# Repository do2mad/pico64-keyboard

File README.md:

# Pico64 Keyboard

> 🇩🇪 **Deutsche Anleitung: [README.de.md](README.de.md)**

A tiny adapter that turns a **Raspberry Pi Pico 2 W** into a wireless keyboard and joystick
interface for the **Commodore 64** – use your phone with the
[Blue-64 Keyboard app](https://github.com/do2mad/blue64-keyboard-ios) (iPhone and Android),
a **Bluetooth keyboard** or a **Bluetooth gamepad** (e.g. 8BitDo).

**Get the app:** iPhone – [TestFlight beta](https://testflight.apple.com/join/jEn4tsP7) · Android – [APK in the latest release](https://github.com/do2mad/blue64-keyboard-ios/releases/latest)

The Pico plugs in between the C64 mainboard and the keyboard cable and emulates the keyboard
matrix in software. Apart from the Pico you only need **17 resistors and one diode** – no level
shifters and no crosspoint switch, because GPIO 0–25 of the RP2350 are 5 V tolerant.
The original keyboard and both joysticks keep working.

## Features

- Emulates the complete 8×8 keyboard matrix plus RESTORE – any number of keys at the same time
- Reacts within about 70 ns to every column the C64 selects (core 1 runs a lookup table from RAM),
  so programs that scan several columns at once work too
- Same Bluetooth LE service as the BT-64 / Blue-64 firmware with the BLE keyboard service –
  the Blue-64 Keyboard app works unchanged (the Pico shows up as **Pico64**)
- Type text and short BASIC listings from the app (snippets)
- **Bluetooth keyboards** (Classic and BLE) – German QWERTZ layout typed as printed, or
  positional mapping for games (F10 switches)
- **Bluetooth gamepads** (8BitDo, Xbox, PlayStation, Switch and many more, via
  [Bluepad32](https://github.com/ricardoquesada/bluepad32)) as **joystick in port 1 or 2**
- App, keyboard and gamepads can be used at the same time; **two app devices** (e.g. iPhone and iPad) at once
- **CBM-II keyboard** by cable or Bluetooth with the [CBM2 Keyboard](https://github.com/do2mad/cbm2-keyboard) adapter (from 0.13.1, socket J3 on the V2 PCB)
- USB keyboard without a C64: the real C64 keyboard on a Mac, PC or MiSTer
- USB console: every line you type in a terminal is typed on the C64, plus a key log for debugging
- Powered by the C64, no extra power supply

## Status

**v0.13.1 – working.** Tested on a breadbin C64 with an iPhone and an Android phone, Bluetooth
keyboards, gamepads and the CBM2 Keyboard. **PCB V2** with the Pico on top (soldered or plugged in)
and the socket for the CBM2 Keyboard – KiCad project, Gerber files, parts list and photos in
[hardware/](hardware/). Bluetooth keyboard and gamepad support still needs testing with more devices.

> **Hardware change in v0.10:** all 17 resistors are now 100 Ω (PA0–PA7 were 1 kΩ). Joystick
> port 2 needs this – everything else also works with the old values. See [docs/HARDWARE.md](docs/HARDWARE.md).

## Getting started

1. **Build the adapter** – PCB (KiCad project, Gerber files, parts list): [hardware/](hardware/); wiring and safety
   notes, also for perfboard: [docs/HARDWARE.md](docs/HARDWARE.md).
   Check the CN1 pinout of your C64 with a multimeter before soldering.
2. **Flash the firmware** – easiest on the [flash page](https://1mhz.de/Pico64/) straight from Chrome
   or Edge. Or: hold BOOTSEL, plug the Pico into your computer, drag
   `pico64-keyboard-vX.Y.Z.uf2` from the [latest release](https://github.com/do2mad/pico64-keyboard/releases/latest)
   onto the `RP2350` drive. Do this with the Pico **out of the C64** or with the C64 switched off.
3. **Plug it in** between CN1 and the keyboard cable, switch the C64 on – the Pico LED blinks
   (nothing connected yet).
4. **Connect with the app** – [Blue-64 Keyboard](https://github.com/do2mad/blue64-keyboard-ios)
   finds the Pico by itself, the LED stays on while connected.
5. **Or pair a Bluetooth keyboard / gamepad** – see below.

Building the firmware yourself: [docs/BUILDING.md](docs/BUILDING.md).
Bluetooth and cable protocol: [docs/PROTOCOL.md](docs/PROTOCOL.md).

## Bluetooth keyboard and gamepad

The Pico looks for keyboards and gamepads all the time. To pair a new one, put it into pairing
mode – it connects by itself within a few seconds (no PIN, no app needed). Paired devices
reconnect automatically when switched on. Up to 4 Bluetooth connections at the same time
(apps, keyboards and gamepads together).

- **Keyboard:** usually hold the Bluetooth / pairing key (or Fn + a channel key) for 3 s, see
  the keyboard's manual. If the keyboard asks for a code, type `0000` and Enter.
- **8BitDo gamepads:** switch on in **Android / D-input mode** (many models: hold **B + Start**)
  or **Switch mode** (**Y + Start**), then hold the pair button for 3 s. Modes differ per model –
  see the 8BitDo manual and the [Bluepad32 list of supported controllers](https://bluepad32.readthedocs.io/).
- **Other gamepads** (Xbox, PlayStation, Switch Pro …): normal pairing mode.

### Keyboard mapping

Two modes, **F10** switches (the USB console shows the current mode):

| Mode | What it does |
|---|---|
| **Symbolic** (default) | Types what is printed on a **German** keyboard: Shift+0 gives `=`, Shift+2 `"`, AltGr+Q `@`, Z and Y in the right place. Characters the C64 doesn't have (ä ö ü ß € …) are ignored. |
| **Positional** | Every key acts like the C64 key at the same place, SHIFT stays SHIFT – best for games and for the graphic characters. |

| PC key | C64 key |
|---|---|
| Esc | RUN/STOP |
| Tab | CTRL |
| Ctrl | CTRL |
| Alt, Windows/Cmd | C= |
| Backspace, Del | INST/DEL |
| Home | CLR/HOME |
| Insert | £ |
| F1 – F8 | F1 – F8 |
| F9, Page Up, Pause | RESTORE |
| Cursor keys | CRSR (up/left with SHIFT automatically) |
| F10 | switch mapping |

### Gamepad

| Gamepad | C64 |
|---|---|
| D-pad or left stick | joystick directions |
| A, B | fire |
| X | SPACE |
| Y | RETURN |
| Select / − | RUN/STOP |
| Start / + | F1 |
| L1 + R1 together | swap joystick port (1 ↔ 2) |

The first gamepad plays on **port 2** (most games), a second one on port 1.

## USB keyboard (without a C64)

Take the board out of the C64, plug the C64 keyboard cable into it and connect the Pico via USB
to a Mac, PC, Raspberry Pi or MiSTer: the **real C64 keyboard becomes a USB keyboard**. The app
and Bluetooth keyboards work at the same time and are sent via USB too.

The Pico decides when it starts: without USB power it can only be powered by the C64 → C64
mode. With USB power it listens for 0.6 s whether a C64 scans the keyboard → C64 mode,
otherwise USB keyboard. If a C64 starts scanning later, the Pico restarts in C64 mode by itself.
A C64 that is switched off but still connected pulls the lines low – the Pico then stays in C64
mode (the USB keyboard only works with the board outside the C64).

Choose the output with **RESTORE + F key** (stored):

| Keys | Output |
|---|---|
| RESTORE + F1 | MiSTer, C64 core (keys as the core expects them; RESTORE alone = F11) |
| RESTORE + F3 | PC, German layout |
| RESTORE + F5 | PC, US layout |
| RESTORE + F7 | Mac, German layout |
| RESTORE + F8 (SHIFT + F7) | Mac, US layout |

PC / Mac: types what is printed on the key (SHIFT + 2 = `"`, SHIFT + `:` = `[`). DEL = Backspace,
INST = Insert, CRSR = cursor keys, F1–F8, HOME / CLR = Home / End, RUN/STOP = Esc, ← = Tab,
CTRL = Ctrl, C= = Win / Cmd, £ = `\`. Like the original, the keyboard has no diodes, so some
three-key combinations show a phantom key.

In the USB console `!u` shows the mode, `!u0` … `!u4` choose the output.

## USB console

Connect the Pico via USB while it sits in the C64 (the diode protects both sides) and open a
terminal with 115200 baud, e.g. `screen /dev/tty.usbmodem* 115200` on a Mac.

- Every line you type is typed on the C64, followed by RETURN (letters unshifted, tokens like
  `~clr~`, `~home~`, `~f1~` work).
- A line with just `d` switches the key log on or off: every key state received via Bluetooth
  and every state applied to the matrix, with timestamps, plus the connection interval.
- `!s` status (app, keyboards, gamepads, joystick ports), `!p` switch keyboard mapping,
  `!b` search for new Bluetooth devices on/off, `!x` forget all paired keyboards / gamepads,
  `!u` USB keyboard mode (see above).

## Safety

- The Pico **never drives a C64 line high** – PB0–PB7, RESTORE and (for joystick 2) PA0–PA4
  are only pulled to GND or released (open drain), like a key switch or a joystick does.
- Use GP0–GP22 only. GP26–GP28 are **not** 5 V tolerant, GP23–25 and GP29 belong to the radio.
- 5 V tolerance only applies while the Pico is powered – which it always is, because it is
  powered by the C64.
- Use at your own risk. Check your wiring twice.

## Related projects

- [Blue-64 Keyboard](https://github.com/do2mad/blue64-keyboard-ios) – the app (iPhone and Android)
- [CBM2 Keyboard](https://github.com/do2mad/cbm2-keyboard) – a CBM-II keyboard (500/600/700) on the C64,
  connected to the Pico64 by cable or Bluetooth
- [Pico USB Keyboard](https://github.com/do2mad/pico-usb-keyboard) – the same app as a USB keyboard:
  a plain Pico 2 W without wiring, for the MiSTer C64 core, PC, Mac or Raspberry Pi
- [BT-64 with BLE keyboard service](https://github.com/do2mad/BT-64/tree/ble-keyboard) – the
  firmware extension for the BT-64 / Blue-64 adapter

## Discussion

Questions, photos, experiences: the thread in the (German) retro forum
[1mhz.de – Pico64-Keyboard, SPL BT-64 oder Blue-64 Tastaturadapter](https://1mhz.de/forum/thread/8761-pico64-keyboard-spl-bt-64-oder-blue-64-tastaturadapter/).
Bug reports and feature requests are also welcome as a GitHub issue.

## Credits & license

- Firmware © 2026 Martin Oswald – [1mhz.de](https://1mhz.de), [MIT License](LICENSE)
- Hardware (schematic, PCB) © 2026 Martin Oswald,
  [CC BY-SA 4.0](LICENSE-HARDWARE.md) – open hardware
- Uses the Raspberry Pi Pico SDK, BTstack, the CYW43 driver and
  [Bluepad32](https://github.com/ricardoquesada/bluepad32) by Ricardo Quesada – see [NOTICE](NOTICE)
- The Bluetooth service follows the protocol of the BLE keyboard extension for
  [BT-64 / Blue-64](https://github.com/sideprojectslab/BT-64) by SideProjectsLab
- C64 keyboard connector pinout after Ruud Baltissen

Changes: [CHANGELOG.md](CHANGELOG.md)

Commodore and Commodore 64 are trademarks of their respective owners. This project is not
affiliated with or endorsed by them, by Raspberry Pi Ltd. or by SideProjectsLab.

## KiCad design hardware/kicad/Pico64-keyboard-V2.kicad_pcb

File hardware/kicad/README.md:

# Pico64 Keyboard – KiCad project (PCB V2)

Open `Pico64-keyboard-V2.kicad_pro` with **KiCad 10**. Everything the project needs is in this
folder: the symbol library `Pico64-keyboard-V2.kicad_sym`, the footprints in
`Pico64-keyboard-V2.pretty/` and the 3D models in `3d/` – the library tables use `${KIPRJMOD}`,
so no global libraries are required.

Licence: CC BY-SA 4.0 (see `../../LICENSE-HARDWARE.md`). The 3D models and several footprints
are based on the KiCad libraries (CC BY-SA 4.0 with the KiCad library exception).

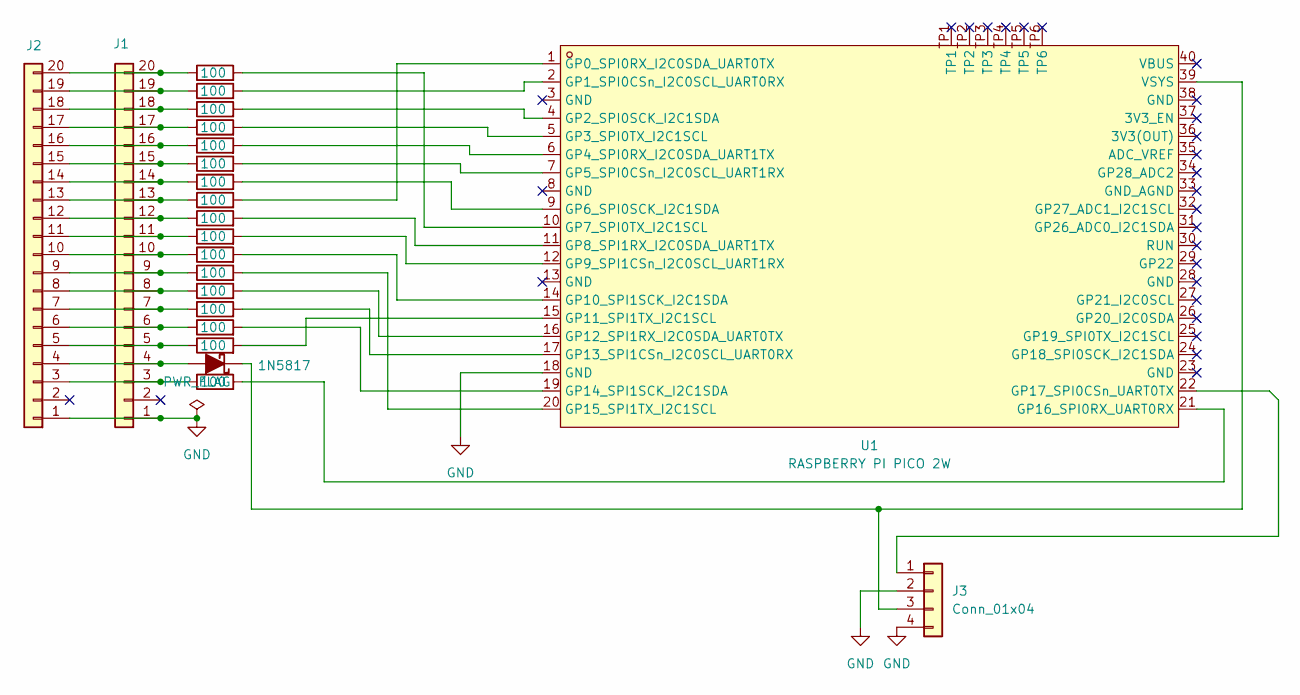
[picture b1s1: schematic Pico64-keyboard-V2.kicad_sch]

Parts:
D1: 1N5817; D_DO-41_SOD81_P7.62mm_Horizontal
J1, J2: Conn_01x20; PinHeader_1x20_P2.54mm_Vertical
J3: Conn_01x04; JST_XH_B4B-XH-A_1x04_P2.50mm_Vertical
R1, R2, R3, R4, R5, R6, R7, R8, R9, R10, R11, R12, R13, R14, R15, R16, R17: 100; R_Axial_DIN0204_L3.6mm_D1.6mm_P7.62mm_Horizontal
U1: RASPBERRY PI PICO 2W; RaspberryPi_Pico_Common_Unspecified; MPN Raspberry Pi Pico 2W; LCSC Part C42394205

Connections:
GND: J1.1, J2.1, J3.2, J3.4, U1.18 (GND)
unnamed: D1.2 (A), J1.4, J2.4
unnamed: D1.1 (K), J3.3, U1.39 (VSYS)
unnamed: J1.3, J2.3, R17.1
unnamed: J1.5, J2.5, R16.1
unnamed: J1.6, J2.6, R15.1
unnamed: J1.7, J2.7, R14.1
unnamed: J1.8, J2.8, R13.1
unnamed: J1.9, J2.9, R12.1
unnamed: J1.10, J2.10, R11.1
unnamed: J1.11, J2.11, R10.1
unnamed: J1.12, J2.12, R9.1
unnamed: J1.13, J2.13, R8.1
unnamed: J1.14, J2.14, R7.1
unnamed: J1.15, J2.15, R6.1
unnamed: J1.16, J2.16, R5.1
unnamed: J1.17, J2.17, R4.1
unnamed: J1.18, J2.18, R3.1
unnamed: J1.19, J2.19, R2.1
unnamed: J1.20, J2.20, R1.1
unnamed: J3.1, U1.22 (GP17_SPI0CSn_UART0TX)
unnamed: R8.2, U1.1 (GP0_SPI0RX_I2C0SDA_UART0TX)
unnamed: R2.2, U1.2 (GP1_SPI0CSn_I2C0SCL_UART0RX)
unnamed: R3.2, U1.4 (GP2_SPI0SCK_I2C1SDA)
unnamed: R4.2, U1.5 (GP3_SPI0TX_I2C1SCL)
unnamed: R5.2, U1.6 (GP4_SPI0RX_I2C0SDA_UART1TX)
unnamed: R6.2, U1.7 (GP5_SPI0CSn_I2C0SCL_UART1RX)
unnamed: R7.2, U1.9 (GP6_SPI0SCK_I2C1SDA)
unnamed: R1.2, U1.10 (GP7_SPI0TX_I2C1SCL)
unnamed: R9.2, U1.11 (GP8_SPI1RX_I2C0SDA_UART1TX)
unnamed: R10.2, U1.12 (GP9_SPI1CSn_I2C0SCL_UART1RX)
unnamed: R11.2, U1.14 (GP10_SPI1SCK_I2C1SDA)
unnamed: R16.2, U1.15 (GP11_SPI1TX_I2C1SCL)
unnamed: R13.2, U1.16 (GP12_SPI1RX_I2C0SDA_UART0TX)
unnamed: R14.2, U1.17 (GP13_SPI1CSn_I2C0SCL_UART0RX)
unnamed: R15.2, U1.19 (GP14_SPI1SCK_I2C1SDA)
unnamed: R12.2, U1.20 (GP15_SPI1TX_I2C1SCL)
unnamed: R17.2, U1.21 (GP16_SPI0RX_UART0RX)

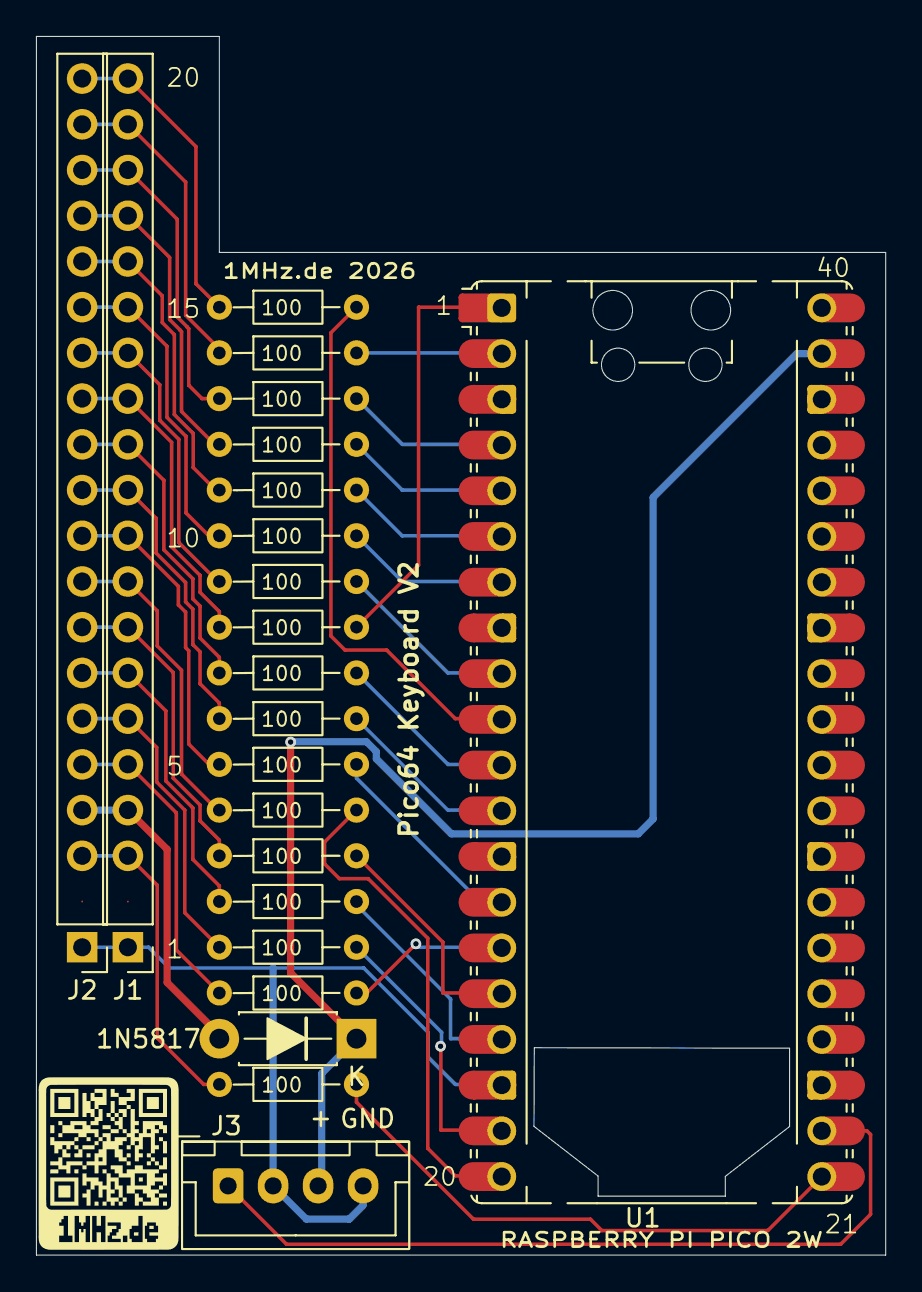
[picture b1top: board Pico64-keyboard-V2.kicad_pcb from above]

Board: 2 copper layers, 47.2 x 67.7 mm, 22 parts (0 on the bottom side), 38 nets.
